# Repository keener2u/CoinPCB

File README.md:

# CoinPCB
Simple Coin Shaped ESP8266 Breakout Board
# V0.2 Errata
 * pins D3,D4,D8 are used for chip bootup to figure out where to run the program from . This causes issues if the Coin is hooked into the board on bootup. 
 * D3,D4 also include a pull up resistor on boot and must be rerun to allow the pins to run to low when turned on.
 * simple work around is to not solder Q1
 * advanced is to exacto knife the D3 trace and run a jumper wire from the D3 pin to the D2 PIN if you aren't going to use the I2C connection. If you do this come see me:)
 * reprogram the chip to get it back into a normal state. You can also plug the wifi board into power, let it boot and then plug the coin into the wifi board.
 https://www.reddit.com/r/esp8266/comments/5ujgfl/issue_powering_up_wemos_d1_mini_with_pins_d3_d4/

# V0.2 Updates
 * Fixed V0.1 issues with LED running to power
 * Added 53 Ohm resistor to 5V line through Infrared
 * Created DHT12 I2C symbol package
 * Changed component naming references to start at D9 after input referencs throug D8
# V0.1 Errata

* D1 LED is setup incorrectly on foot print d1 polarization is wrong  
* the infrared transmitter footprint needs to be rotated so the emitter is pointing out on the next rev  
* D3 and D2 LED need to be run to ground instead of power  
* use an exacto knife to cut the traces between 3.3VCC and D3 and Vcc and D4
* use an exacto knife to scrape the top layer off to make the copper ground plane visible, jumper the copper ground plane to the two 100ohm resistors  
* input pin D3 is already on a 1k pull down so there is no need to add another resistor. 
* you can just jumper R1 across the two pads.

# Updates for Next Version
add a spot for a pwm to run a servo
break out the rest of GPIO lines onto the board
add a coincell holder with a power switch

# To Do
Create a how-to on setting up KiCad with the newest symbol and footprint libraries as well as how to import digikey libraries.

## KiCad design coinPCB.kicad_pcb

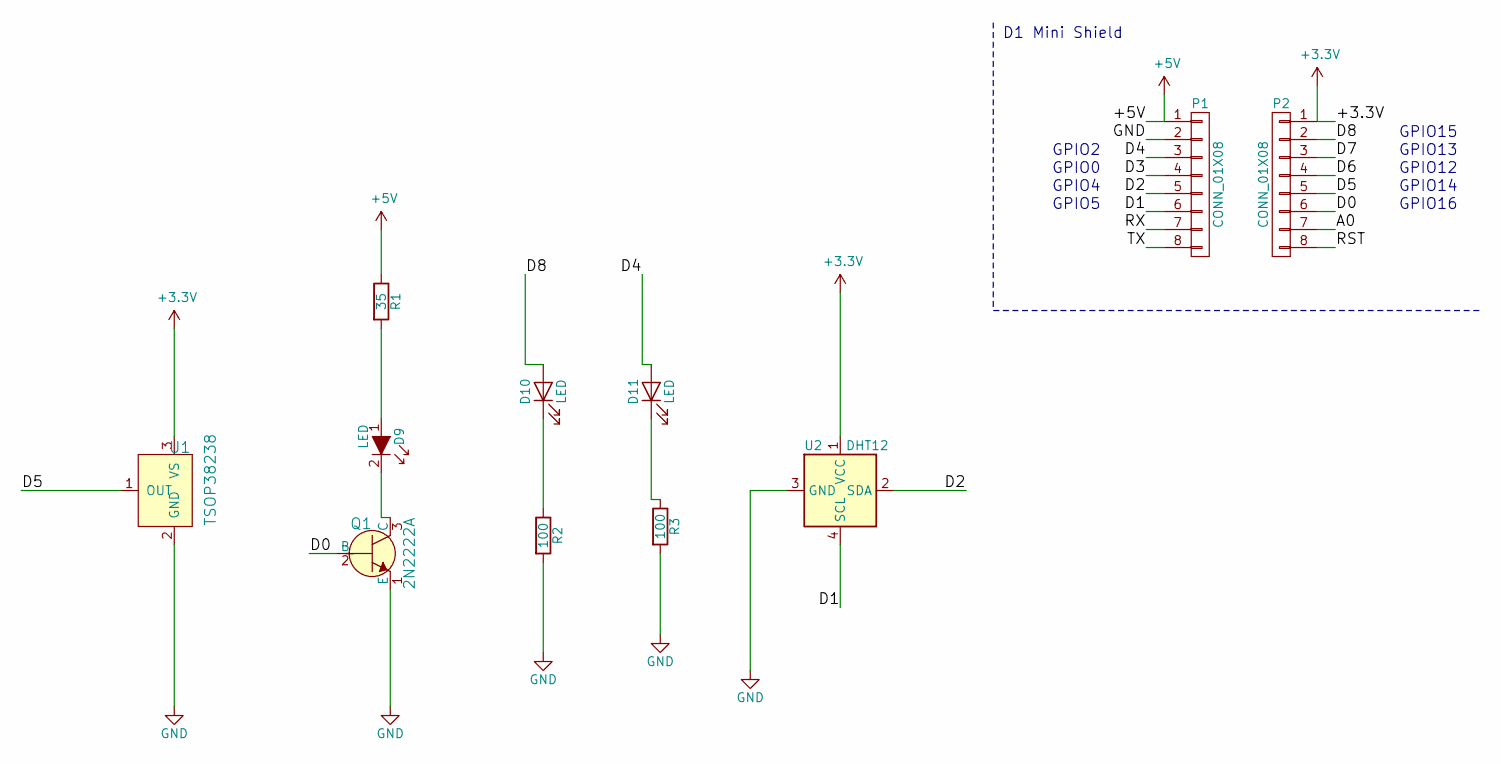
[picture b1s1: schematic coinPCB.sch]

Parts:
D9: LED; LED_IR_TSAL6100
D10, D11: LED; LED_3mm_Radial
P1, P2: CONN_01X08; D1_mini_Pin_Header
Q1: 2N2222A; TO-18-3; MPN 2N2222A; Digi-Key_PN 2N2222ACS-ND
R1: 35; R_Axial_DIN0204_L3.6mm_D1.6mm_P7.62mm_Horizontal
R2, R3: 100; R_Axial_DIN0204_L3.6mm_D1.6mm_P7.62mm_Horizontal
U1: TSOP38238; IR_Receiver_TSOP38238; MPN TSOP38238; Digi-Key_PN 751-1227-ND
U2: DHT12; Aosong_DHT11_5.5x12.0_P2.54mm

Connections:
+3V3: P2.1, U1.3 (VS), U2.1 (VCC)
+5V: P1.1, R1.1
/A0: P2.7
/D0: P2.6, Q1.2 (B)
/D1: P1.6, U2.4 (SCL)
/D2: P1.5, U2.2 (SDA)
/D3: P1.4
/D4: D11.2 (A), P1.3
/D5: P2.5, U1.1 (OUT)
/D6: P2.4
/D7: P2.3
/D8: D10.2 (A), P2.2
/RST: P2.8
/RX: P1.7
/TX: P1.8
GND: P1.2, Q1.1 (E), R2.2, R3.2, U1.2 (GND), U2.3 (GND)
unnamed: D9.1, R1.2
unnamed: D9.2, Q1.3 (C)
unnamed: D10.1 (K), R2.1
unnamed: D11.1 (K), R3.1

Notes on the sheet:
GPIO2
GPIO0
GPIO4
GPIO5
GPIO15
GPIO13
GPIO12
GPIO14
GPIO16
D1 Mini Shield

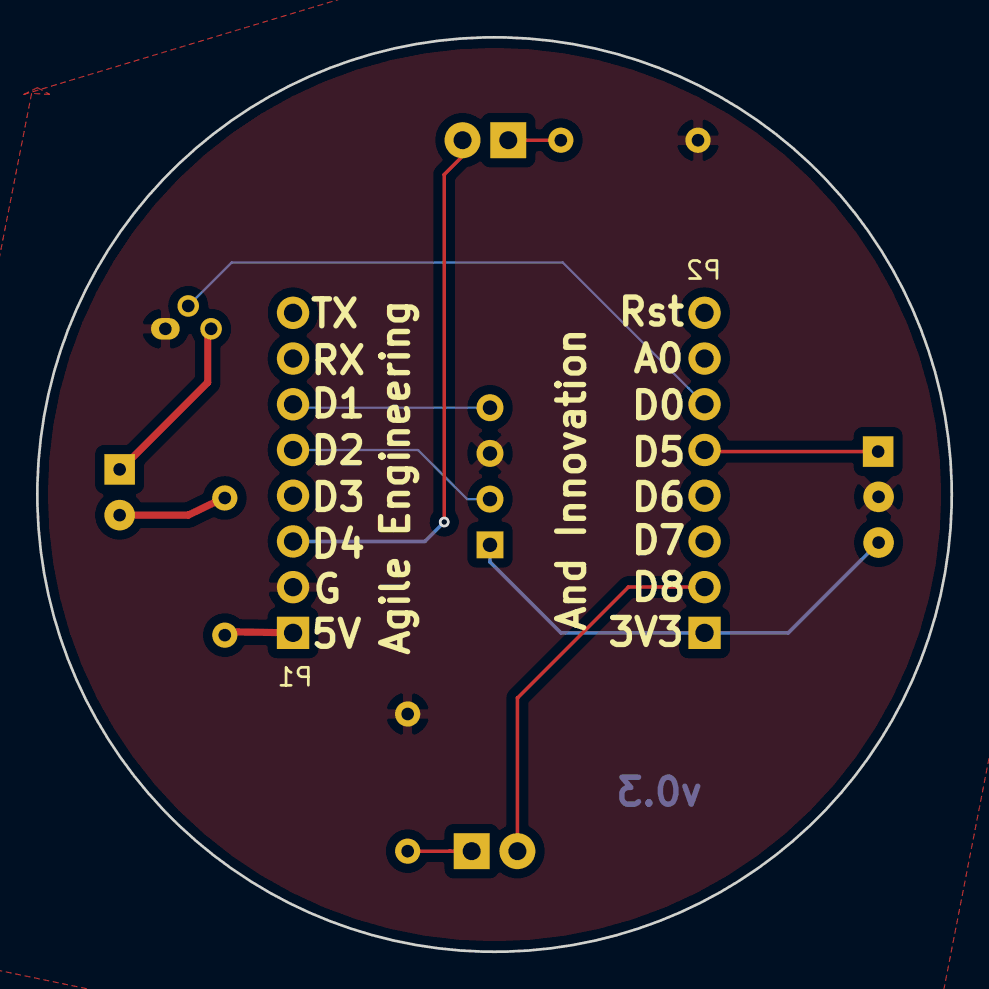
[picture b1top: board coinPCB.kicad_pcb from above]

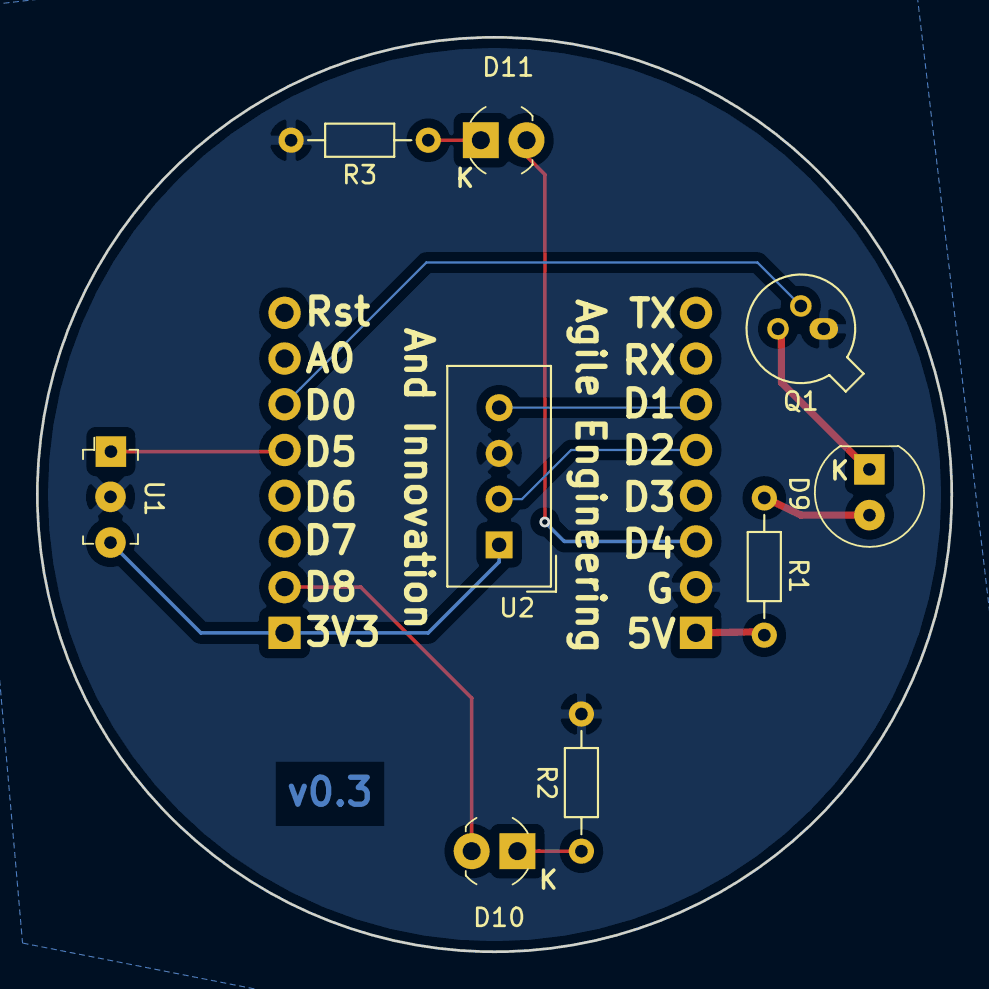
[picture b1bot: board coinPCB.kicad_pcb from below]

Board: 2 copper layers, 50.8 x 50.8 mm, 11 parts (9 on the bottom side), 13 nets.

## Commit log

2019-04-25 first spin v01 includes I2C, 2 LEDS, 1 infrared transmitter and 1 infrared reciever
2019-04-26 fixed DHT11 symbol on schematic, need to update to DHT12 when I find it
2019-05-01 Updated README with Errata section
2019-05-03 added DHT12 symbol to project lib. Still uses DHT11 footprint
2019-05-03 cleaning up folder and using git ignore
2019-05-03 updated symbols to new KiCad Library and digikey library
2019-05-03 fixed all errors and should build correctly
2019-05-03 fixed schematic errors, including taking out 1k resitor from D3 because that pin as pull-up resistor arleady, and running D4 and D8 to ground
2019-05-03 began laying out v0.2 with digikeyfootprins
2019-05-03 finished initial PCB trace layout and added the copper backplane as well as fixed the digi-key model of the IR_LED_TSAL_6100 to have the Cathode be the square pad.
2019-05-03 added v0.2 draft with 3d model of components on top
2019-05-03 added supporting documents
2019-05-08 added final resitor values to 5v line
2019-05-08 updated gerber files and sent to manufacturing. SHIP IT
2019-05-09 updated PDF schematic and fixed library symbol pointer in KiCAD
2019-08-23 Update README.md
    Updated with issues on coin V0.2 that will be fixed for V0.3
2019-08-23 adding pictures of how to build the coin step by step thanks @dellistech
2019-08-23 Moved over IR TX pin to D0 because of issues with D3 Pull-up at boot time.
2019-08-25 v0.3 update with gbr files
2019-08-26 updating ignore to not keep cached save files
2019-11-25 changing DigiKey to be part of a project library
2019-11-25 finalized moving footprint and symbol libraries to shared place to work with the KiCAD Dockerfile.

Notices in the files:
coinPCB.kicad_pcb:
License: CC BY-SA 4.0
coinPCB.sch:
Licnese: CC BY-SA 4.0
creativecommons.org/licences/by/4.0
